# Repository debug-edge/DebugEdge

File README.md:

# Debug Edge
A small bridge board to link a programmer to a PCB, via a card edge connector.
See [debug-edge.io](https://debug-edge.io/) for more the full specification and rationale.

## Goals

A nice, easy to use debug/flash probe adapter that can quickly and easily connect to a board, staying put as you need it!

## Concept

Greg Davill [mentioned](https://twitter.com/GregDavill/status/1298419285086199808) coming across the AVX Open Ended Card Edge connector, and Scott Shawcroft [followed up](https://twitter.com/tannewt/status/1298422601811808256) that it'd be a good idea to explore a conversion from a typical 10-pin SWD/JTAG connector to the card edge format.

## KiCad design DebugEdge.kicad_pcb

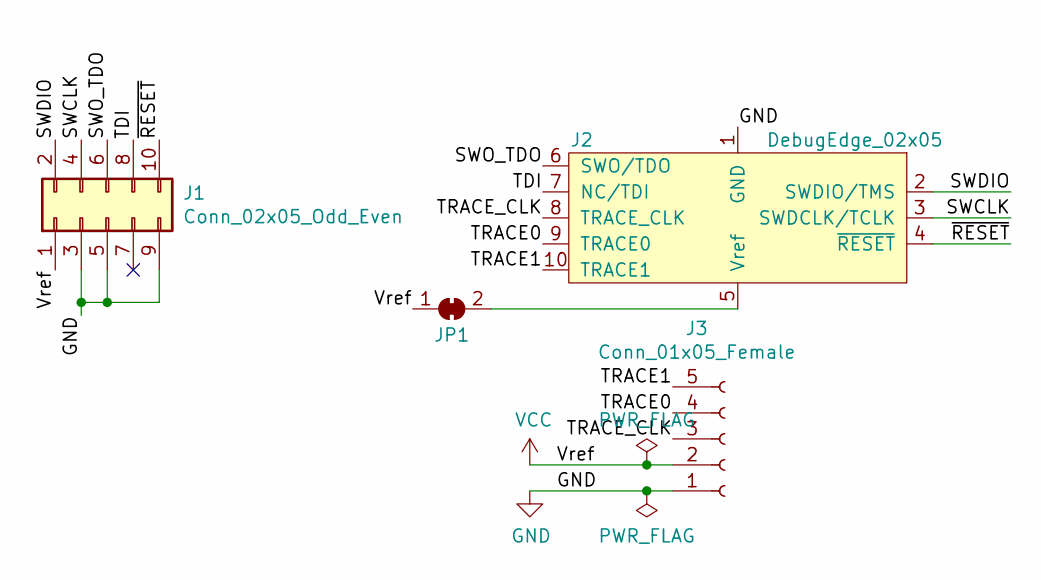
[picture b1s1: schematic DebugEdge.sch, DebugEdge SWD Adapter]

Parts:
J1: Conn_02x05_Odd_Even; PinHeader_2x05_P1.27mm_Vertical_SMD
J2: DebugEdge_02x05; DebugEdge_2x05_Host
J3: Conn_01x05_Female; PinSocket_1x05_P2.54mm_Vertical
JP1: SolderJumper_2_Bridged; SolderJumper-2_P1.3mm_Bridged_RoundedPad1.0x1.5mm

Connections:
/SWCLK: J1.4, J2.3 (SWDCLK/TCLK)
/SWDIO: J1.2, J2.2 (SWDIO/TMS)
/SWO_TDO: J1.6, J2.6 (SWO/TDO)
/TDI: J1.8, J2.7 (NC/TDI)
/TRACE0: J2.9 (TRACE0), J3.4
/TRACE1: J2.10 (TRACE1), J3.5
/TRACE_CLK: J2.8 (TRACE_CLK), J3.3
/~RESET~: J1.10, J2.4 (~RESET~)
GND: J1.3, J1.5, J1.9, J2.1 (GND), J3.1
unnamed: J2.5 (Vref), JP1.2 (B)
VCC: J1.1, J3.2, JP1.1 (A)

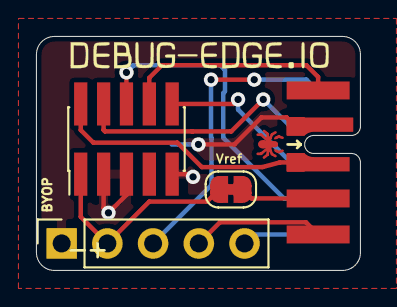
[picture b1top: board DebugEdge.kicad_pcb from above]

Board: 2 copper layers, 18.0 x 13.0 mm, 5 parts (0 on the bottom side), 11 nets.

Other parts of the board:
Ref**: Val**; DebugEdge_URL_Silk

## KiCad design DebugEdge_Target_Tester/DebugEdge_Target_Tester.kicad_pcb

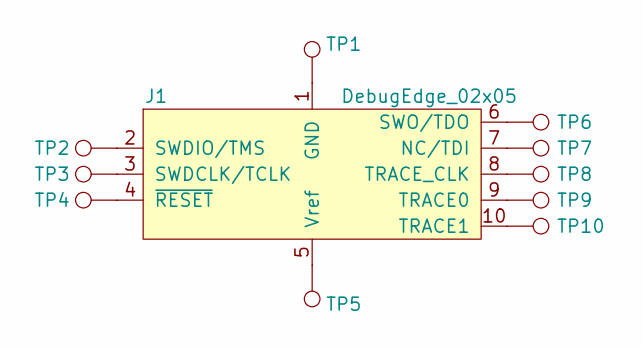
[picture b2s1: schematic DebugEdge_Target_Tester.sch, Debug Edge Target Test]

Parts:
J1: DebugEdge_02x05; DebugEdge_2x05_Target
TP1, TP2, TP3, TP4, TP5, TP6, TP7, TP8, TP9, TP10: TestPoint; Pin_D1.0mm_L10.0mm

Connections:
unnamed: J1.1 (GND), TP1.1
unnamed: J1.2 (SWDIO/TMS), TP2.1
unnamed: J1.3 (SWDCLK/TCLK), TP3.1
unnamed: J1.4 (~RESET~), TP4.1
unnamed: J1.5 (Vref), TP5.1
unnamed: J1.6 (SWO/TDO), TP6.1
unnamed: J1.7 (NC/TDI), TP7.1
unnamed: J1.8 (TRACE_CLK), TP8.1
unnamed: J1.9 (TRACE0), TP9.1
unnamed: J1.10 (TRACE1), TP10.1

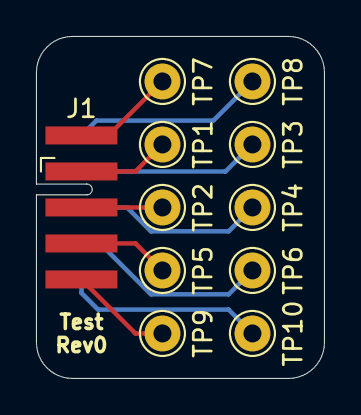
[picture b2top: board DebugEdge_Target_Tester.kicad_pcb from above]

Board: 2 copper layers, 16.0 x 19.0 mm, 12 parts (1 on the bottom side), 10 nets.

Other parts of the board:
Ref**: Val**; DebugEdge_URL_Silk

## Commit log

2020-08-26 First revision of OpenClip.
2020-08-26 Renaming OpenClip to DebugEdge, adopt v1 of 10 pinout.
2020-08-26 Change license to Apache-2.0 WITH SHL-21.
    Doesn't have to stay under this, I just find this a nice, very permissive hardware license!
2020-08-27 Add solder bridge for Vref & BYOP pins.
    BYOP in case you need to bring your own power!
2020-08-27 Fix pin 1 silk, add 2x5 target FP.
2020-08-27 Fix mask on bottom. Remove paste.
2020-08-27 Add target test board.
2020-08-27 Expanded edge to let ground pour flow.
    And rounded the corners, cause why not?
2020-08-27 Expanded board.
    Gives more room for a box header if one is used.
2020-08-28 Taper pads and add silk to top side
2020-08-28 Port the tapers to footprint.
2020-09-06 Updated both Host and Target footprints with the new design Spider/MCU icon Extended GND pin 1.0mm slot (as its hard to fab 0.6mm it seems)
2020-09-13 New spider and MCU icons
2020-09-13 Add 2x2, 2x3, 2x4 Debug Edge symbols.
2020-09-13 Added 2x2, 2x3, 2x4 target edge footprints.
2020-09-13 Marked the 2x5 footprints virtual.
2020-09-13 Added comments to fp/sym tables.
2020-09-27 Update host adapter to new footprint
2020-11-09 Remove outdated image
2020-11-09 Link to website and provide images on readme
2020-11-27 change 2x5 adapter to swd/jtag pinout
2020-11-29 Added footprints for pcb-rnd layout editor
2020-11-29 refined pcb-rnd layout editor footprint geometry and terminals
2020-11-29 pcb-rnd version of DebugEdge_Target_Tester layout and png
2020-11-29 added DebugEdge in pcb-rnd format and png
2020-11-29 fixed via thermals in pcb-rnd format DebugEdge.lht
2020-12-03 Add a proposal for exposing the front-side pads on the back side, to ease pogo-programming
